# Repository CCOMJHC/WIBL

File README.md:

# Low-cost Data Logger System

## Purpose

This repository contains the hardware designs, firmware source code, and supporting applications and libraries for a low-cost data logger aimed at the NMEA ([National Marine Electronics Association](https://www.nmea.org)) 0183 and 2000 protocols, as used in many marine electronics systems.  The goal is to provide a minimally-functional system to record the data appearing on NMEA0183 and NMEA2000 busses on board ships, which can be used to provide volunteer depth observations (and many other things) to assist in mapping the oceans.

## Why Have Another Logger?

There is a robust infrastructure of data loggers for both NMEA0183 and NMEA2000 busses, but they are often intended for different purposes (e.g., voyage data recorders, WiFi gateways, etc.), and they are typically order US$250 [2020] or more.  This project came out of efforts within the [Seabed 2030](https://seabed2030.gebco.net) project to map the world ocean completely by 2030, where large-scale mapping is required if the goals of the programme are to be met.  Consequently, while volunteer data is a part of the solution, it has to be something that can be scaled to very large data collections.  Since it has proven hard to sustain open data collection of this type (most of the sustained efforts have been closed, with data only going back to the collectors, and not to open databases), we believe that the only viable financial model for this purpose is to give the hardware away for free, rather than attempting to sell it for profit.  That is, the hardware is free to the data collector, who is asked just to host the hardware on their ship.  Because of this model, we need the hardware to be as low-cost as possible.

This project is therefore aimed at designing as simple, and low-cost, a logger as possible, so that as many as possible can be built and distributed to assist in mapping the oceans.  The target price is order US$30 [2020] for one interface (either NMEA0183 or NMEA2000), or US$40 [2020] for both interfaces.

At the same time, we recognise that getting data from the loggers into the national and international databases can be difficult, and ask a lot of the volunteer data collectors.  The project is therefore also attempting to define a workflow for submission of data to the [International Hydrographic Office](https://iho.int)'s [Data Center for Digital Bathymetry](https://www.ngdc.noaa.gov/iho/), hosted by the [National Centers for Environmental Information](https://www.ngdc.noaa.gov) in Boulder, CO.  The goal is to have a "Trusted Node in a Box", so that anyone wanting to support collection of data of this kind has everything they need to support a very basic data flowpath direct from the loggers through the cloud to DCDB.  (Developers are then free to add on anything else they need.)

## What Does the Logger Do?

The logger's functionality is deliberately constrained.  During normal operations, the logger monitors the NMEA0183 and/or NMEA2000 busses to which it is attached, and records any valid data packet received to local storage.  Timestamps are provided through the elapsed time counter on the microcontroller used, and although a pseudo-time is computed from NMEA2000 data packets if they are available, there is no expectation that timestamps will be assigned until the data is uploaded for processing.

The logger provides a WiFi interface for monitoring, configuration, and control.  If there's no other option, the logger will provide its own access point (i.e., create its own WiFi network) to which users can connect, but it can also be configured to connect to a mobile hotspot or an infrastructure WiFi network if available.  The logger runs a web server so that any modern browser can be used to interact with the system (the logger provides the HTML and JavaScript for all required functionality), and also provides an API to send simple commands using a custom language and receive JSON-format responses for a programmatic interface.

After upload to a mobile collection device (e.g., a cell-phone or tablet), or direct uploading (via a separate upload server, also included, if the logger is on an infrastructure network with internet connection), the data is sent to Amazon Web Services, at which point it is processed, reformatted, packaged, and transmitted to DCDB for archive.

## Concept of Operations

This logger is designed for supported, focussed, data collections.  In this mode, loggers would be provided by an organisation in a specific geographic location to support data collection in a particular area.  The goal here is to provide density of observations in an area, which greatly assists in processing the data, and making useful products.  In addition to providing the loggers (and recruiting the volunteer observers), the organisation would also provide local support personnel to visit the volunteer observers, pick up the collected data (via mobile device or through maintaining an upload server), and make sure that the loggers were still collecting data.  Having local support also ensures that there is continued communication with the observers, which is useful in sustaining the community in the long term.

After each visit, all of the data collected (potentially from multiple observers) on the mobile device can be uploaded to any available service that implements the cloud segment of the software suite.  This could be something set up specifically for the organisation using the model provided here, or it could be a third-party that provides an equivalent.

## Licensing and Distribution

In order to provide for the widest possible use (and to avoid excuses ...) the hardware designs, firmware source, and supporting libraries are all released as Open Source under the MIT license.  The cloud segment is released under the MIT License for non-commercial use; for commercial licenses, please contact info@ccom.unh.edu.

## Where to Start

See the "Logger firmware" section below to get started with the WIBL loggers. 
See the "Data management" section below to get started using WIBL and 
`wibl-python` tools to manage and process data generated by WIBL loggers.

### Logger firmware

The source for the system is maintained in a [GitHub repository](https://github.com/CCOMJHC/WIBL), which also includes a [Wiki](https://github.com/CCOMJHC/WIBL/wiki) for details of the design and system development.  The Wiki is the most useful source of current information to set up and programme the logger firmware, and to access the rest of the code resources.

To build the firmware and work with the hardware designs, you will need at least:

1. A functional Python interpreter (at least 3.13) (e.g., [MiniConda](https://www.anaconda.com/docs/getting-started/miniconda/main)).

2. A working copy of [VSCode](https://code.visualstudio.com) and [PlatformIO](https://platformio.org) to build the firmware and other logger functionality.

3. Support for NMEA2000 handling on ESP32 (you need the [base library](https://github.com/ttlappalainen/NMEA2000) and [ESP-specific](https://github.com/ttlappalainen/NMEA2000_esp32) extensions).

4. [KiCAD](https://www.kicad.org) (at least 9.0) to examine and edit the logger schematic and board layout.

5. [FreeCAD](https://www.freecad.org) (at least 1.0) to examine and edit the logger enclosure STEP files.

6. A working C++11 (at least) compiler for the software data simulator (the installation with VSCode works very well).

With these prerequisites, the recommended place to start is with the logger firmware, followed by the post-processing Python code, which will allow you to demonstrate that your logger is actually logging data.  For benchtop testing, the hardware data simulator can be used to generate simulated data on both NMEA0183 and NMEA2000 buses for testing logger modifications.

### Data management

The included [wibl-python](wibl-python/README.md) tools allow data from WIBL 
loggers to be processed into GeoJSON format and to be submitted to 
[DCDB](https://www.ngdc.noaa.gov/iho/). There is also a tool called 
[LogConvert](LogConvert) that allows data from TeamSurv and Yacht Devices
loggers to be converted to WIBL format for further processing using 
`wibl-python`.

An easy way to use both `wibl-python` and `LogConvert` is to use the official
WIBL [container images](DataManagement/containers/README.md).

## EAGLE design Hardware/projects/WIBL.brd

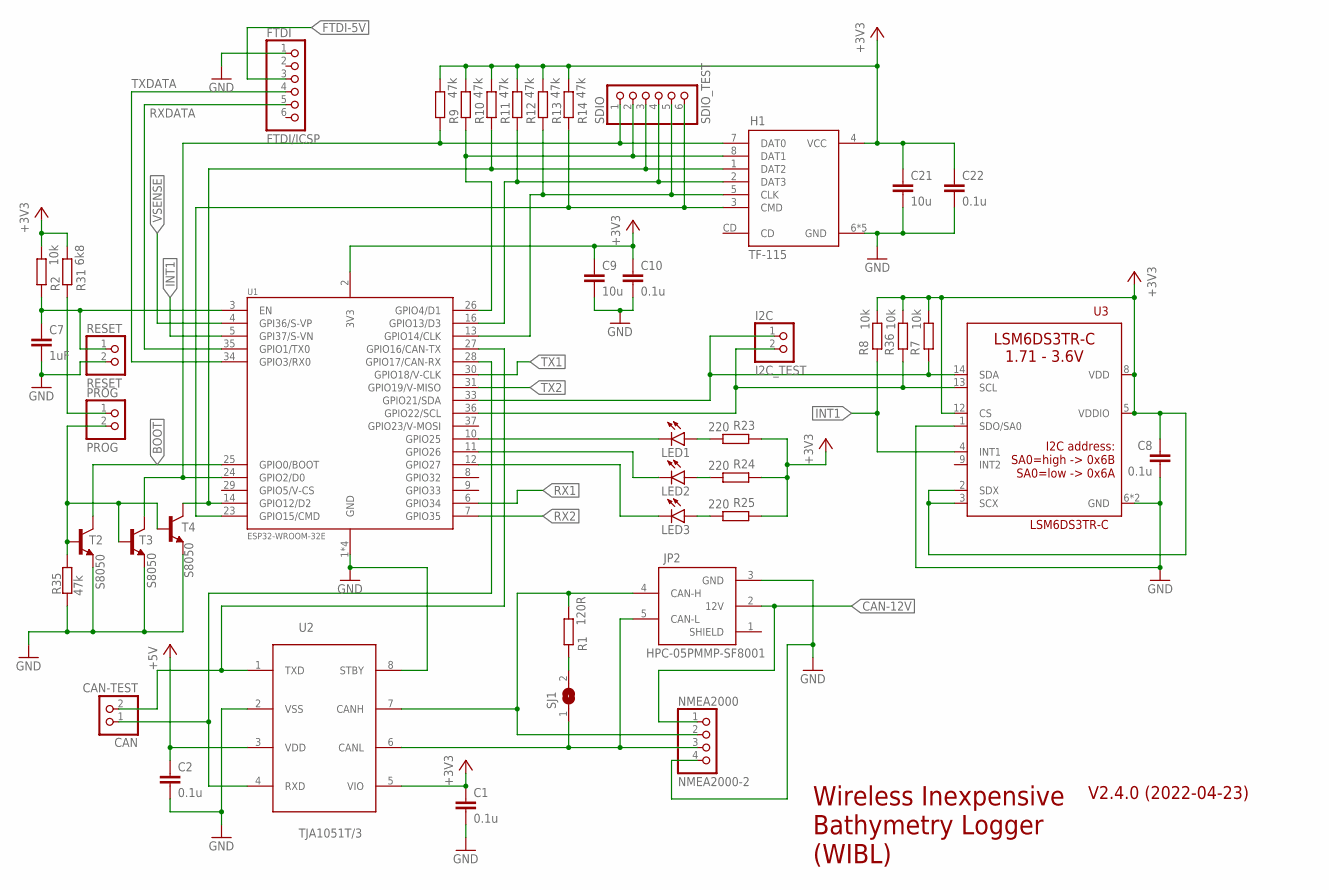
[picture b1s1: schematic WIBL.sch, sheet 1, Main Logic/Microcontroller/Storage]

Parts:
C1, C2, C8, C10, C22: 0.1u; C0805
C7: 1uF; C0805
C9, C21: 10u; C0805
CAN: CAN-TEST; 1X02
FTDI: FTDI/ICSP; 1X06
H1: TF-115; XUNPU-MICROSD-SOCKET
I2C: I2C_TEST; 1X02
JP2: HPC-05PMMP-SF8001; NMEA2000
LED1, LED2, LED3: LEDCHIP-LED0603; CHIP-LED0603
NMEA2000: NMEA2000-2; 1X04
PROG: PROG; 1X02
R1: 120R; R0805
R2, R7, R8, R36: 10k; R0805
R9, R10, R11, R12, R13, R14, R35: 47k; R0805
R23, R24, R25: 220; R0805
R31: 6k8; R0805
RESET: RESET; 1X02
SDIO: SDIO_TEST; 1X06
SJ1: SJ
T2, T3, T4: S8050; SOT23
U1: ESP32-WROOM-32E; ESPS32-WROOM-32E
U2: TJA1051T/3; SOIC8
U3: LSM6DS3TR-C; LGA-14-2.5X3MM

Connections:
+3V3: C1.1, C8.1, C9.1, C10.1, C21.1, C22.1, H1.4 (VCC), R2.2, R7.2, R8.2, R9.2, R10.2, R11.2, R12.2, R13.2, R14.2, R23.1, R24.1, R25.1, R31.2, R36.2, U1.2 (3V3), U2.5 (VIO), U3.2 (SDX), U3.3 (SCX), U3.5 (VDDIO), U3.8 (VDD), U3.12 (CS); also elsewhere on the board
+5V: C2.1, U2.3 (VDD); also elsewhere on the board
BOOT: T2.3 (C), U1.25 (GPIO0/BOOT); also elsewhere on the board
CAN-12V: JP2.2 (12V), NMEA2000.1; also elsewhere on the board
FTDI-5V: FTDI.3; also elsewhere on the board
GND: C1.2, C2.2, C7.2, C8.2, C9.2, C10.2, C21.2, C22.2, FTDI.1, H1.6 (GND), H1.GND1 (GND), H1.GND2 (GND), H1.GND3 (GND), H1.GND4 (GND), JP2.3 (GND), NMEA2000.4, R35.1, RESET.2, T2.2 (E), T3.2 (E), T4.2 (E), U1.1 (GND), U1.15 (GND), U1.38 (GND), U1.THERM (GND), U2.2 (VSS), U2.8 (STBY), U3.1 (SDO/SA0), U3.6 (GND), U3.7 (GND); also elsewhere on the board
INT1: R8.1, U1.5 (GPI37/S-VN), U3.4 (INT1)
unnamed: JP2.4 (CAN-H), NMEA2000.2, R1.2, U2.7 (CANH)
unnamed: JP2.5 (CAN-L), NMEA2000.3, SJ1.1, U2.6 (CANL)
unnamed: R1.1, SJ1.2
unnamed: C7.1, R2.1, RESET.1, U1.3 (EN)
unnamed: CAN.2, U1.27 (GPIO16/CAN-TX), U2.1 (TXD)
unnamed: CAN.1, U1.28 (GPIO17/CAN-RX), U2.4 (RXD)
unnamed: H1.1 (DAT2), R11.1, SDIO.3, T4.3 (C), U1.14 (GPIO12/D2)
unnamed: H1.8 (DAT1), R10.1, SDIO.2, U1.26 (GPIO4/D1)
unnamed: H1.7 (DAT0), R9.1, SDIO.1, T3.3 (C), U1.24 (GPIO2/D0)
unnamed: H1.2 (DAT3), R12.1, SDIO.4, U1.16 (GPIO13/D3)
unnamed: H1.5 (CLK), R13.1, SDIO.5, U1.13 (GPIO14/CLK)
unnamed: H1.3 (CMD), R14.1, SDIO.6, U1.23 (GPIO15/CMD)
unnamed: LED1.C, U1.10 (GPIO25)
unnamed: LED2.C, U1.11 (GPIO26)
unnamed: PROG.2, R35.2, T2.1 (B), T3.1 (B), T4.1 (B)
unnamed: LED3.C, U1.12 (GPIO27)
unnamed: LED1.A, R23.2
unnamed: LED2.A, R24.2
unnamed: PROG.1, R31.1
unnamed: LED3.A, R25.2
RX1: U1.6 (GPIO34); also elsewhere on the board
RX2: U1.7 (GPIO35); also elsewhere on the board
RXDATA: FTDI.5, U1.35 (GPIO1/TX0)
SCL: I2C.1, R7.1, U1.33 (GPIO21/SDA), U3.14 (SDA)
SDA: I2C.2, R36.1, U1.36 (GPIO22/SCL), U3.13 (SCL)
TX1: U1.30 (GPIO18/V-CLK); also elsewhere on the board
TX2: U1.31 (GPIO19/V-MISO); also elsewhere on the board
TXDATA: FTDI.4, U1.34 (GPIO3/RX0)
VSENSE: U1.4 (GPI36/S-VP); also elsewhere on the board

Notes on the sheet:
Wireless Inexpensive Bathymetry Logger (WIBL)
V2.4.0 (2022-04-23)

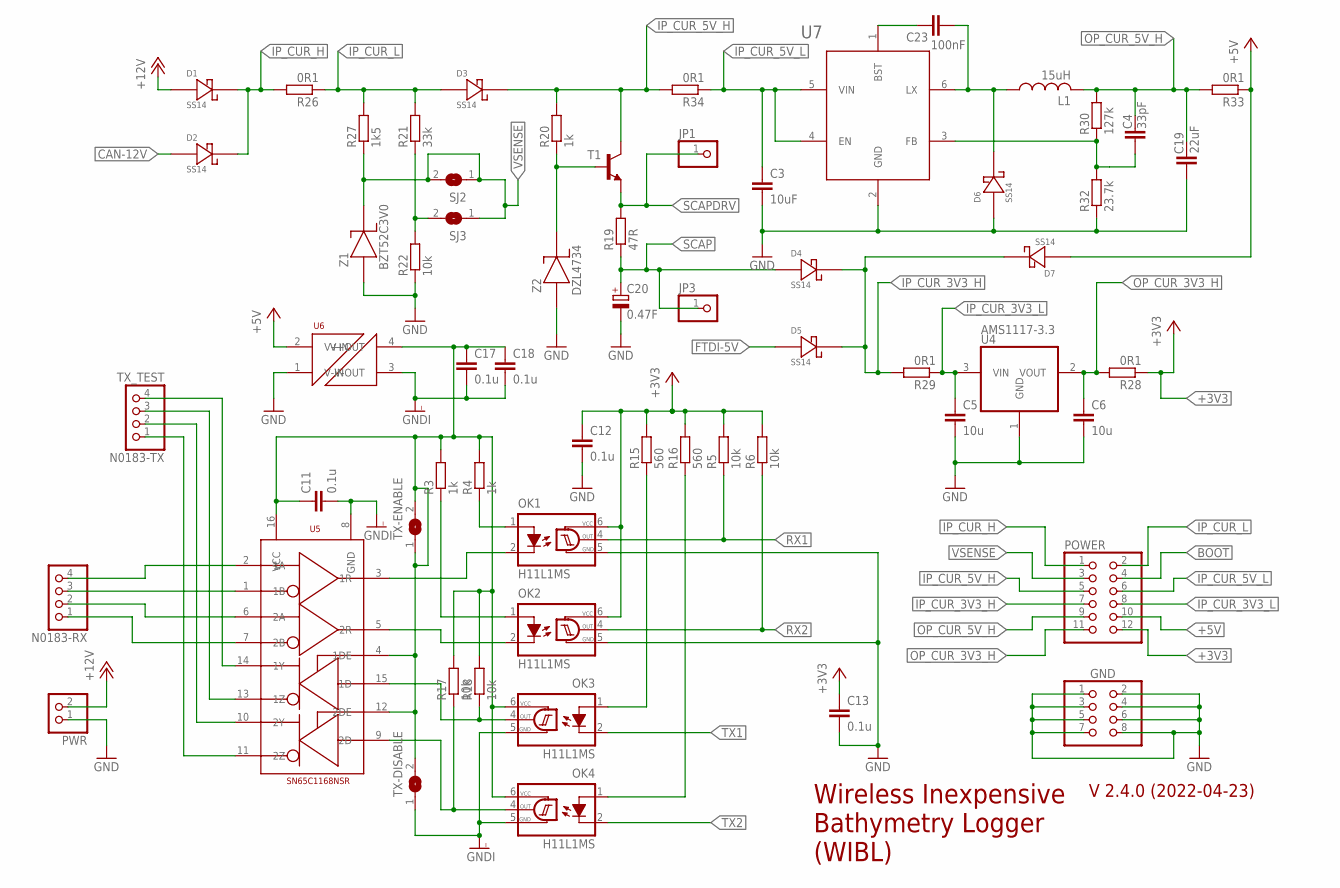
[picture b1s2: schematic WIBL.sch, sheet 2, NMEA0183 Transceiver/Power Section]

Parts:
C3: 10uF; C1206
C4: 33pF; C0603
C5, C6: 10u; C0805
C11, C12, C13, C17, C18: 0.1u; C0805
C19: 22uF; C0603
C20: 0.47F; P128-50
C23: 100nF; C0402
D1, D2, D3, D4, D5, D6, D7: SS14; DO-214AC
GND: PINHD-2X4; 2X04
JP1, JP3: PINHD-1X1; 1X01
L1: 15uH; MWSA0603S
N0183-RX: PINHD-1X4; 1X04
N0183-TX: TX_TEST; 1X04
OK1, OK2, OK3, OK4: H11L1MS; DIL6-SMD
POWER: PINHD-2X6; 2X06
PWR: PINHD-1X2; 1X02
R3, R4, R20: 1k; R0805
R5, R6, R17, R18, R22: 10k; R0805
R15, R16: 560; R0805
R19: 47R; R0805
R21: 33k; R0805
R26, R28, R29, R33, R34: 0R1; R0603
R27: 1k5; R0805
R30: 127k; R0603
R32: 23.7k; R0603
SJ2, SJ3: SJ
T1: BC817-16-NPN-SOT23-BEC; SOT23-BEC
TX-DISABLE: SJ
TX-ENABLE: SJ
U4: AMS1117-3.3; SOT223
U5: SN65C1168NSR; SOIC16
U6: RFM-0505S
U7: BL9352A; SOT-23-6L
Z1: BZT52C3V0; SOD123
Z2: DZL4734; SOD-123FL

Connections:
+3V3: C12.1, C13.1, OK1.6 (VCC), OK2.6 (VCC), POWER.12, R5.2, R6.2, R15.2, R16.2, R28.1; also elsewhere on the board
+5V: D7.A, POWER.10, R33.1, U6.2 (V+IN); also elsewhere on the board
+12V: D1.A, PWR.2
BOOT: POWER.4; also elsewhere on the board
CAN-12V: D2.A; also elsewhere on the board
FTDI-5V: D5.A; also elsewhere on the board
GND: C3.2, C5.2, C6.2, C12.2, C13.2, C19.1, C20.-, D6.A, GND.1, GND.2, GND.3, GND.4, GND.5, GND.6, GND.7, GND.8, OK1.5 (GND), OK2.5 (GND), PWR.1, R22.1, R32.1, U4.1 (GND), U6.1 (V-IN), U7.2 (GND), Z1.1 (A), Z2.A; also elsewhere on the board
GNDI: C11.2, C17.2, C18.2, OK3.5 (GND), OK4.5 (GND), TX-DISABLE.1, U5.8 (GND), U6.3 (V-OUT)
IP_CUR_3V3_H: D4.K, D5.K, D7.K, POWER.7, R29.2
IP_CUR_3V3_L: C5.1, POWER.8, R29.1, U4.3 (VIN)
IP_CUR_5V_H: D3.K, POWER.5, R20.2, R34.2, T1.C
IP_CUR_5V_L: C3.1, POWER.6, R34.1, U7.4 (EN), U7.5 (VIN)
IP_CUR_H: D1.K, D2.K, POWER.1, R26.2
IP_CUR_L: D3.A, POWER.2, R21.2, R26.1, R27.2
unnamed: OK1.2 (C), U5.3 (1R)
unnamed: OK2.2 (C), U5.5 (2R)
unnamed: OK1.1 (A), R4.1
unnamed: OK2.1 (A), R3.1
unnamed: N0183-RX.4, U5.2 (1A)
unnamed: N0183-RX.3, U5.1 (1B)
unnamed: N0183-RX.2, U5.6 (2A)
unnamed: N0183-RX.1, U5.7 (2B)
unnamed: C11.1, C17.1, C18.1, OK3.6 (VCC), OK4.6 (VCC), R3.2, R4.2, R17.2, R18.2, TX-DISABLE.2, TX-ENABLE.1, TX-ENABLE.2, U5.4 (1DE), U5.12 (2DE), U5.16 (VCC), U6.4 (V+OUT)
unnamed: N0183-TX.4, U5.14 (1Y)
unnamed: N0183-TX.3, U5.13 (1Z)
unnamed: N0183-TX.2, U5.10 (2Y)
unnamed: N0183-TX.1, U5.11 (2Z)
unnamed: OK3.1 (A), R15.1
unnamed: OK4.1 (A), R16.1
unnamed: OK3.4 (OUT), R18.1, U5.15 (1D)
unnamed: OK4.4 (OUT), R17.1, U5.9 (2D)
unnamed: R20.1, T1.B, Z2.K
unnamed: C23.P$1 (1), U7.1 (BST)
unnamed: C23.P$2 (2), D6.K, L1.P$1 (1), U7.6 (LX)
unnamed: R21.1, R22.2, SJ3.2
unnamed: C4.1, R30.1, R32.2, U7.3 (FB)
OP_CUR_3V3_H: C6.1, POWER.11, R28.2, U4.2 (VOUT)
OP_CUR_5V_H: C4.2, C19.2, L1.P$2 (2), POWER.9, R30.2, R33.2
RX1: OK1.4 (OUT), R5.1; also elsewhere on the board
RX2: OK2.4 (OUT), R6.1; also elsewhere on the board
SCAP: C20.+, D4.A, JP3.1, R19.1
SCAPDRV: JP1.1, R19.2, T1.E
TX1: OK3.2 (C); also elsewhere on the board
TX2: OK4.2 (C); also elsewhere on the board
VSENSE: POWER.3, R27.1, SJ2.1, SJ2.2, SJ3.1, Z1.2 (K); also elsewhere on the board

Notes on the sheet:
Wireless Inexpensive Bathymetry Logger (WIBL)
V 2.4.0 (2022-04-23)

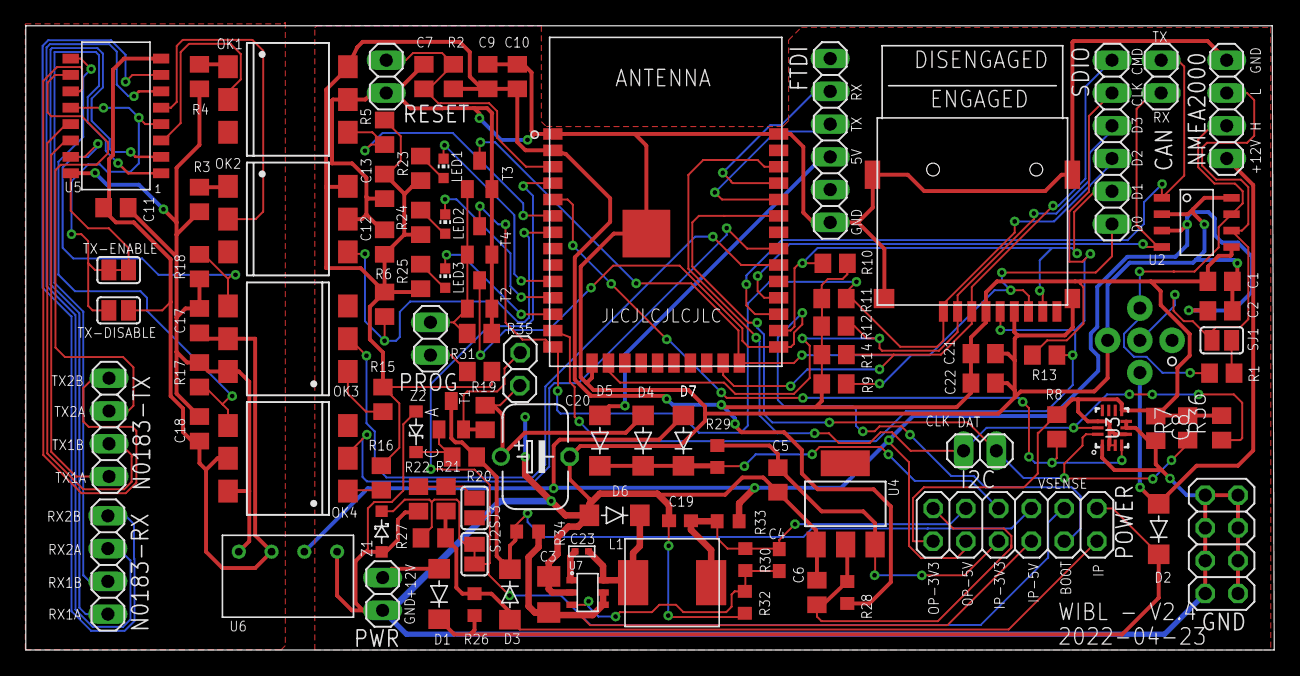
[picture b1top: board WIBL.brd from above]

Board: 2 copper layers, 96.8 x 48.4 mm, 105 parts (0 on the bottom side), 70 nets.

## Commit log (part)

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2025-03-19 Fixed Localstack start up scripting
2025-03-25 New ProcessWibl
    This new version no longer exits out of the loop when a file fails to convert to GeoJSON due to a lack of information. Files unable to be transformed are documented in a CSV for record-keeping.
2025-03-26 #65 Update metadata handling on GeoJSON conversion to assume OpenVBI-compatible B-12 metadata
2025-03-27 Convert script for tsv and dat
2025-04-04 Refactor Open Layers JS into separate file
2025-04-21 Documented code.
2025-04-25 #65 Add note to README about default CRS in GeoJSON metadata templates
2025-05-07 wibl-python: Update readme: move not on metadata format to the more relevant Edit WIBL file section
2025-05-22 wibl-python: Converted processing PowerShell script to LF endings, rather than CRLF, for consistency.
2025-05-22 fw: bump version to 1.5.4
2025-05-23 fw: updated release notes for 1.5.4 release.
2025-05-23 fw: Added mDNS responder to WiFi
    This addition ensures that the WiFi system starts an mDNS responder when either the AP starts or station connects, so that the logger is resolvable as "logger.local" using any modern OS and browser.
2025-05-24 fw: release notes for 1.5.5
2025-05-27 Added validation, submission, and conversion start lambdas
2025-05-28 Bug fixes
2025-05-28 Fixed pathing
2025-05-29 lambda packaging: move to src-layout packag structure to ensure package autodiscovery is safe and reliable (more info: https://setuptools.pypa.io/en/latest/userguide/package_discovery.html#src-layout)
2025-06-01 OpenLayers Integration
2025-06-01 Restored Static Folder
2025-06-01 Created a tap that contains an empty Mapbox map.
2025-06-01 Establishing frontend and manager connection
2025-06-02 Restore accidentally deleted files
2025-06-10 WIP Geojson download
2025-06-10 Filter debugging / Linked detail table clearing
2025-06-17 Starting dashboard
2025-06-18 Get all endpoint
2025-06-23 Fixed static collection
2025-06-26 Continued Overhaul
2025-06-27 Started wibl_data transition
2025-07-02 Continued Development on wibl and geojson data transition
2025-07-07 Download and Save FastAPI implementation for WIBL/GeoJSON
2025-07-10 Changed WIBL metadata to include average lat/lon and total depth in metres.
2025-07-14 Dashboard update interval selection and polling.
2025-07-16 Separate frontend & manager into separate db containers / Migrate postgis db to include bounding boxs
2025-07-21 Refactoring out dash in place of plotly JS
2025-07-23 Static Dashboard
2025-07-25 Bounding box display on dashboard map
2025-07-28 Comments / Removed deltas / implemented observations used gauge
2025-07-29 wibl-python: Debug local-only commands after conversion to use click library
2025-07-30 wibl-python: Add localstack docker config for automated testing of uploadwibl without cloud
2025-07-30 wibl-python: Update documentation to reflect click-based CLI; Update wibl integration test to add validate command; Update test suite metadata to conform to B-12 3.1; Update config parsing to add def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
2025-07-31 wibl-python: Document strict mode processing of WIBL files
2025-07-31 Updating Doc Strings / Adding Comments
2025-08-29 fw: outline for a batch download using tar+gz library (responding to GET on a particular endpoint).
2025-09-02 fw: fixes for streaming an archived tar/gz file of all logs.
2025-09-03 fw: updates to website for archive download, bug-fixes to support. Moves command processor to 1.4.1.
2025-09-03 Adjusting GeoJSONStatus bitwise applications / GeoJSONStatus unit tests
2025-09-18 Unit test changes
2025-10-14 fw: Small edit to clean up 1.6.0 PR (82)
2025-10-15 upload-server: Add initial (not quite working) localstack configuration to allow local testing of S3 uploads; Document how to test uploads using curl
2025-10-15 upload-server: Add reference to script to build add-logger command
2025-10-15 upload-server: Add initial README
2025-10-15 upload-server: Add support for overriding AWS endpoint to facilitate local testing; Make SNS topic optional, if not defined in config, skip notification on upload
2025-10-15 upload-server: Begin refactor of configuration to make cloud deployment simpler
2025-10-15 upload-server: Refactor security group to use rules to enable both SSH and HTTPS access
2025-10-15 upload-server: Add Elastic IP so that upload server can be accessed via a persistent IP address
2025-10-15 upload-server: Add AWS access and secret to wibl-upload compose configuration used for local testing; Add example of reading bucket data via aws cli
2025-10-15 upload-server: Start sketching out terraform config
2025-10-15 upload-server: Add add-logger script to deployment
2025-10-15 upload-server: Start refactoring cert generation to use terraform TLS provider
2025-10-15 upload-server: Add policies and role for access S3 and SNS from EC2 instance
2025-10-15 upload-server: Document Terraform deployment and configuring and testing the instance
2025-10-15 upload-server: Debug userdata script to enable systemctl service for upload-server that survives reboot
2025-10-15 upload-server: Un-comment logging of CHECKIN status now that logging has been refactored
2025-10-15 upload-server: Fix typos; Add trusted node prefix to example logger identifiers
2025-10-16 upload-server: fix typos; include terraform.lock.hcl; add .terraform directory to gitignore
2025-10-20 upload-server: CloudWatch agent: Enable removal of logs that have been uploaded to CloudWatch
2025-10-27 wibl-python: cloud: AWS: Update conversion start lambda permissions as per https://docs.aws.amazon.com/lambda/latest/dg/urls-auth.html#urls-auth-none
2025-10-30 FW: Updates for supply voltage monitoring with hardware v 2.5.1, including the value being reported in status JSON, and on the website.
2025-10-30 Creating new terraform module parallel to configure-manager-ecs.sh
2025-10-31 Upload: fixed comments to reflect full implementation.
2025-11-01 Upload: added configuration parameter for CA certificate so that we can retrieve it from add-logger and report as part of the configuration package.
2025-11-04 FW: Updates to supply monitor to clean up a little.
2025-11-05 HWSim: Restructured to make N2K and N1K follow the same simulator message sequence, which limits traffic on N2K bus, but at least allows it to vary!
2025-11-07 Updated top-level README to bring things up to date.
2025-11-24 Addition of v2.5.1 hardware design files
    This archives the Eagle CAD files for 2.4.1 and adds the KiCAD files for v2.5.1, and supporting information.
2025-11-24 Renaming STEP files for enclosures for consistency.
2025-11-24 Clean-up of KiCAD project files.
2025-12-04 HW: Updates for 2.5.1 hardware release using KiCAD files.
2025-12-04 Small modification for brackets in hardware simulator (functionally identical, but safer).
2025-12-08 Updates to mechanical drawings and STLs for hardware 2.5.1 enclosures.
    Added STL files for 2.5.1 enclosures, bringing the archive up to date; added mechanical drawings for the new enclosure.
2025-12-09 upload-server: fix typo: Document Docker multi-platform builds on Linux AMD64 hosts
2025-12-11 upload-server: Add link to IAM console
2025-12-24 LogConvert: Add script to build statically linked binary in macOS
2025-12-29 Initial bug fixes
2026-01-07 Frontend RDS instance / Expanded container definitions / Cloudwatch groups / ECS one off tasks
2026-01-14 Implementing Django s3 static storage / Static file adjustments / Frontend/Manager setup task changes
2026-01-14 data-management: Update Docker image Dockerfile and documentation for 1.2.0 release
2026-01-20 Stubbing out configuration interface, library, and GNSS integration into main routine.
2026-01-23 UploadServer: Add note on configuration backend in main.tf as well as terraform.tfvars
2026-01-23 Cloudfront additions, vpc permission changes, static bucket access changes
2026-01-28 Changing Bulma to correct file extension / addressing cors issues with static files
2026-02-25 wibl-python: Update rasterio dependency to allow installation under Python 3.14
2026-03-10 UploadServer: Add note to use the DNS name for UploadServer instead of IP address when configuring loggers to do auto-uploads
2026-03-19 Fixing state implementation
2026-03-23 Update validateWibl.ps1 to have clearer failure messages
    Hi, I am so bad at github and I have no idea if this is the right way to do this. Please let me know if this works.
    I am trying to make the validation more obvious so that we don't have to search black and white text for "successfully validated ..." or "failed to vaildate..."
2026-03-26 Fix issue with mismatched commandProc versions.
2026-03-28 refinement of tweeks to ensure enough mem is avialable for dropbox upload.
2026-03-31 Fix map to include style and glyph information
2026-04-02 Add ability to convert both .dat and .tsv to .WIBL
2026-04-07 Adding SSM auth string management / Submission lambda bug fixes / Manager Statistics endpoint bug fixes
2026-05-11 Move Terraform folder into AWS folder / Add build instruction / add descriptions to variables in the main variables.tf file / remove unnecessary definition files.
2026-05-12 Allow JSON to be moved directly into the WiFi message buffer
    I'm running into situations where a large JSON document is being
    successfully generated, but then allocation fails when trying to copy
    it into ESP32WiFiAdapter::m_messages.
    Move semantics to the rescue!
2026-05-12 Store ESP32WiFiAdapter::m_messages by value instead of pointer
    Keeping the document itself on the heap only introduced complexity
    which we didn't really need.
    Also store the default buffer size in a named constant.
2026-05-12 Show question marks for missing file detail fields
    Previously any missing field would cause the whole row to be dropped.
    Given that MD5 hashes aren't guaranteed to be present, that felt like
    overkill.
2026-05-12 Avoid holding a large JSON document while initiating SSL connections
    We ran into issues with allocation failures when attempting to set up
    SSL connections. After a lot of searching and trial-and-error, we
    realized that as the number of log files on the SD card grew, the size
    of the JSON document returned by GenerateFilelist() grew to consume a
    significant chunk of heap memory. This document was resident while the
    upload loop ran, which is the exact time we needed the memory most.
2026-05-12 Allow CountLogFiles to optionally determine total size
    My goal is to pull the file list out of the status JSON document, which
    will require calculating the total file count and size separately from
    the full file list.
2026-05-12 Documentation changes / removing commented code / adding extra nat gateway and routing table for public/private subnet 2
2026-05-15 Adding s3 state storage for the wibl-python terraform configuration
2026-05-18 Adding secret generation script, changing readme to include the script.
2026-05-18 Fixing statistics endpoint bug / Adding plotly as static instead of cdn delivery / removing commented out code
2026-05-19 Add optional WPA3/PMF configuration parameters for Station mode (#111)
    - Adds CONFIG_REQUIRE_PMF_S to allow users with modern hotspots (like Pixel 9 Pro) to enforce Protected Management Frames.
    - Defaults PMF to capable but not required to preserve compatibility with legacy WPA2 networks.
    - Sets sae_pwe_h2e to WPA3_SAE_PWE_BOTH where available to enable WPA3 SAE flow.
2026-05-19 feat(wifi): implement async AP fallback and hotspot recovery scanning
    Replaces the hard ESP.restart() failure loop when Station connection exhausts its retries. Instead:
    - State machine drops to AP-Fallback mode headlessly via apSetup()
    - Triggers non-blocking background async scans WiFi.scanNetworks(true)
    - Polls for configured hotspot presence over the air
    - Transitions seamlessly back to Station mode if detected
    - Configured via new parameter CONFIG_STATION_SCAN_INTERVAL_S exposed to Web UI (default: 30000 ms / 30s)
2026-05-19 fix(wifi): robust WPA3 baseband reset and connection retry handling
2026-05-20 Updating README to account for manual variable replacement in the s3 state storage module.
2026-05-27 Fixing the bounding box bug.
2026-05-27 Updated README for upload server, and pinned localstack (for local test) to v.4.8.1 so that we can run without having to use a license.
2026-05-28 Updating documentation / Removing auth files from git (tfvars, default_auth) / Changing file names / Adding prototype files

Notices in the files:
Hardware/projects/WIBL.brd:
(c) 2022 Center for Coastal and Ocean Mapping
